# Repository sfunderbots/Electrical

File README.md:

# Electrical

This is a repository containing all of the electrical board designs of The Bots, including firmware for the chicker board, which is contained in that sub-folder. 

The robot contains five custom PCBs (not including the Raspberry Pi).

All five boards contained on our robot (six including the Raspberry Pi), for context, are listed as follows:
1. Raspberry Pi 4 - Main Robot Computer and link between the active running computer running our team's software
2. [Faceplate](https://github.com/sfunderbots/Electrical/tree/main/FacePlate) - Connector between Raspberry Pi and Midplate for CANBUS communication, peripherals, and LCD screen eyes
3. [Midplate](https://github.com/sfunderbots/Electrical/tree/main/MidPlate) - Battery input and power distribution (doubles as a mechanical chassis)
4. [Chicker](https://github.com/sfunderbots/Electrical/tree/main/Chicker) - High Voltage Flyback Capacitor Charger and Solenoid Driver
5. [Simovr](https://github.com/sfunderbots/Electrical/tree/main/PAC5527Driver) - A BLDC Motor Driver designed based on the Tinymovr platform in a smaller footprint
6. [Baseplate](https://github.com/sfunderbots/Electrical/tree/main/BasePlate) - Power distribution and CANBUS distribution for the Simovr's, and breakbeam circuits to detect the ball

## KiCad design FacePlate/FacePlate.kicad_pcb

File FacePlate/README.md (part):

# Faceplate Board V2 Documentation

## Overview
---

The Faceplate[^1], one of five of our robot's on board custom PCBs (not including the Raspberry Pi), is a connector and peripheral board between the Raspberry Pi and the rest of the robot system. As this documentation pertains to the Robocup Small Size League Autonomous Soccer, this documentation will be very specific in its use case. The new version of the faceplate incorporates connectors for mouse sensors (localization improvement) and an offboard IMU (placed closer to the center of the robot with less vibration). All five boards contained on our robot (six including the Raspberry Pi), for context, are listed as follows:
1. Raspberry Pi 4 - Main Robot Computer and link between the active running computer running our team's software
2. Faceplate[^1] - Connector between Raspberry Pi and Midplate for CANBUS communication, peripherals, and LCD screen eyes
3. Midplate - Battery input and power distribution (doubles as a mechanical chassis)
4. Chicker[^2] - High Voltage Flyback Capacitor Charger and Solenoid Driver
5. Simovr[^3] - A BLDC Motor Driver designed based on the Tinymovr platform in a smaller footprint
6. Baseplate - Power distribution and CANBUS distribution for the Simovr's, and breakbeam circuits to detect the ball

[^1]: Aptly named due to our robot's circular LCD displays
[^2]: Named after a combination of the flexibility of both kicking or chipping circuits
[^3]: Aptly named after its creator, Simon, and its reference design, the Tinymovr

The Faceplate can be seen on the front of our robot, with the eyes visible and the board covered by a 3D printed piece below:

This guide will serve as a way of a tutorial to design this or a similar board in your own projects, for which we recommend to use JLCPCB as a PCB manufacturer - wew users can register through the link below and receive up to $123 in coupons: [New User](https://jlcpcb.com/?from=Newv).1

## Schematics
---
  
For any of the following schematics, it is useful to group components into a schematic library file inside the EDA tool you are using - in this case, KiCad. Saving custom schematics ensures that when you update a board design you carry over any modifications like manufacturer part numbers, JLC part numbers (LCSC), price, etc. The following serves as an example for what information is useful to keep in the schematic part.

> [!TIP]
> If you select "edit symbol library", you will see that it opens up the library tab in KiCad, which has all of our parts listed. The same information for the LDO as above is here as well.
> <p align="center">
> 
> </p>

> [!IMPORTANT]
> You will need to add your library path to the .KICAD_SYM schematic library file, which stores all of your components. While separating the components into groups hasnt been done yet on our end due to time constraints, we recommend grouping these components by type in separate .KICAD_SYM files to increase productivity.
> <p align="center">
> 
> </p>

Additionally, for each symbol in your library, an associated footprint needs to be added to each symbol used in the schematics, which will be covered in the layout section.

### Power
From the midplate, the Faceplate receives a regulated 5V supply for the Raspberry Pi at 3A, including the CANBUS which is wired all throughout our robot for between-board communication. Specifically, this uses a JST XH connector, which is easily sourced among hobbyists. Then, the board also steps this down to 3.3V for the onboard logic circuits needed such as peripherals and LCD screens. Bypass and decoupling capacitors are needed on the Low Voltage Regulator (LDO) to help maintain power stability, and is chosen over a DC/DC converter due to low current requirements.

<div style="display: flex; gap: 10px;">

</div>

> [!NOTE]
> The part chosen as shown (SOT-223 package) can handle up to 1A of current, which was significantly over specification for our needs.

> [!TIP]
> Always remember to double check the current requirements and heat generation of your system, especially for power conversion!

### Connection to Raspberry Pi
Since the Raspberry Pi 4 has a 40x2 standard dupont style 2.54mm pitch connector, it is easiest to attach a board to board connector of the same type for this PCB. To line it up with the Raspberry Pi, it was easily accomplished by measuring the placement of the 40 pin header in a CAD program (in our case, Onshape) and comparing it to the PCB.

> [!IMPORTANT]
> Special consideration must be taken for ensuring no physical interferences between parts on the bottom layer and the Raspberry Pi, and the top layer to the LCD screens.

### LCD Displays (eyes)
Our LCD displays are a circular GC9A LCD display for which the board is then covered by custom-made 3D printed material for protection surrounding the eyes. Each display (and corresponding breakout board) attaches to a standard 7x1 Dupont style 2.54mm pitch connector, and includes decoupling power capacitors for the 3.3V logic rail to maintain chip operation during normal operating transients. The parts are organized into hierarchical sheets for better organization and viewing of schematics.

### CANBUS
In order to communicate on the CANBUS, one needs to convert the standard SPI interface on the Raspberry Pi to a CAN interface, using a CAN controller (MCP2515T), and a CAN transceiver (SN65HVD233). The CAN controller operates on an 8MHz clock and communicates with a CAN transceiver to send and receive commands over the CANBUS interface. As with the displays, the CAN interface is grouped into a hierarchical sheet to simplify organization.

### Mouse Sensors
Two 8-pin JST GH series connectors link the Raspberry Pi with two identical custom PCBs using a Pixart Imaging PMW3360DM-T2QU navigation sensor, which will be placed at the base of the robot on either side. This will provide significant improvement to our localization and control of the robot, incorporating precice movement of sensors near the surface of the playing field. 

The board files of the mouse sensor can be found on our github page under [PWM3360_PCB_JST](https://github.com/sfunderbots/Electrical/tree/main/pmw3360-pcb-main/pmw3360_pcb_jst), which was modified from the github user siderakb to add a JST connector.

### IMU
For this revision of the faceplate, we have removed the direct connection of the IMU on the faceplate in place of an external connector to be wired to an IMU, in our case chosen as a breakout board from Adafruit: [4438](https://www.adafruit.com/product/4438). This will provide accurate 6-DoF for the robot to improve robot control speed. This is connected using a 4 pin JST PH connector (Adafruit calls it the STEMMA QT QWIIC) which provides both power and data lines.

## Layout
---

The layout of this board and boards in general can be described by the following seven steps:
1. Footprint Libraries (for schematic)
2. Board Setup (Layers and Shape)
3. Part Placment
4. DRC Rules (including differential pairs)
5. Power routing (including zones / polygons)
6. Signal routing (best practices)
7. Custom Rule Areas (e.g. clearance / keepouts) 

The following image shows the overall layout of the board, where red refers to the top layer, blue refers to the bottom layer, green refers to the inner 1 / power layer, and orange refers to the inner 2 / ground layer. These planes on the board make up the 4 layers for the most common PCB to be fabricated, with power layers included for better power distribution, and signals routed generally on the top and bottom layers, if possible.

Below reference most of the important shortcuts on the top bar used in KiCad: On the far left shows the board setup, then on the right past the lock and unlock icons are the footprint library editor, footprint library browser, 3D viewer, import changes from schematic, and DRC rules. 

### Footprint Libraries
Setting up the footprints for each component can be accomplished manually or by downloading a footprint from an EDA library online. One should always consult the datasheet to confirm the validity of the suggested layout. As an example, the 3.3V LDO mentioned in the symbol library section is shown below. One should always verify the validity of a footprint by downloading the 3D model of the part so that the pins will have sufficient solder area and are easy enough to rework with a soldering iron. 

> [!NOTE]
> One can access pre-built footprint files for your EDA tool of choice from libraries such as [snapeda.com](https://www.snapeda.com/home/) or [ultralibrarian.com](https://www.ultralibrarian.com/) for example. Many more exist, but these are the most frequently used. Always remember to verify these footprints as they may not match the datasheet.

> [!IMPORTANT]
> It is especially important to pay attention to drill sizes on through hole parts, as even half a millimeter of difference from the part size may be enough to cause interference during fabrication. For this reason we always recommend to check the "confirm production files" and "confirm part placement", so that the JLCPCB engineers can review your board and catch any issues before they are manufactured.

Lastly, with the same process as the symbol libraries, you need to ensure the path to the footprint library exists in the global or project path directories, so that KiCad knows where to look for this board when you place parts.

### Board Setup
Clicking the gear icon in the top left of the screen on the PCB editor in KiCad, you can access the Board Setup menu. In this menu you can select the number of layers on your board you intend to use, using the "Physical Stackup" submenu, and can define the type of layer used to help KiCad understand how you intend to use this board by using the "Board Editor Layers" submenu. 

> [!NOTE]
> This menu can be confusing, but most of this information can be ignored as when you upload your design to JLCPCB the selection menu for PCB type and layer stackup types is all done on their website. Here, the most important thing to remember is simply to select the number of layers used - usually 2, 4 or 6 depending on complexity of the signal routing.
> <p align="center">
> 
></p>

The shape of the PCB can be defined by creating a bounding box (or whatever closed shape you prefer) with the Edge Cuts Layer. First clicking on the edge cuts layer on the side bar shown below you can define a PCB shape using lines or arcs to create the shape of the board. As long as it is a closed shape, this will work and you can check the 3D view to verify it cut properly. The following shows an example when your board shape is malformed versus closed. When the board shape is closed, the shape will be filled in with a subtle grey tone, and the 3D model will be formed.

<div style="display: flex; gap: 10px;">

</div>

> [!TIP]
> As one can see, it is not always obvious when a board shape is malformed as seen by the above example, where two lines were clearly removed but the overall shape looks the same. As a general rule, the board shape will always fit to the largest area KiCad sees as possible on the Edge Cuts layer, hence how below the shape does not follow any of the drawn lines below.
> 

### Part Placement
When placing parts on the PCB one should think ahead where the power routing will go. In this case, the I would anticipate that the 5V net for the Raspberry Pi would go near the edge of the board and wrap around to the rightmost pins on the 40 pin header, with the 3.3V being the main power plane on the board. Secondly, one should leave enough space around parts to make it easier to solder if rework must be completed, or if you are soldering the boards yourselves. For the faceplate below, you can see that it was ideal to put our power and CAN connector (JST XH 4 pin) on the same side as our power switch and power connector on the midplate. The rest of the components will be arranged in similar fashion leaving enough space for connecting vias for power connection.

To help your process in laying out the PCB parts, you can see the "ratnest" of white lines across the board, which show you where the pads will be connected according to the schematic. 

> [!IMPORTANT]
> It is also super important at this time to pay attention to any missing ratnest wires or pads that do not have any connection, which may be a mistake on the schematic. For this reason I always label my net names on the schematic so that when laying out the PCB it will be obvious if something is missing.

> [!TIP]
> It is always useful to include mounting holes on the PCB so that you can attach the board to an enclosure, which may not be necessary for prototyping but it will be necessary in the end - therefore getting it out of the way early will avoid headaches in the future!
>
> Lastly, one should avoid placing components too close to the edge of the board, especially if the board is panelized, as any stresses to the PCB may cause early failure in certain components, such as PCB mount capacitors (not radial caps). A guide about part placement for proper power and signal delivery can be seen on the JLCPCB website here: [JLCPCB design guidelines for placement and routing](https://jlcpcb.com/blog/pcb-design-guidelines-placement-and-routing).

### DRC Rules

On any board project, DRC rules should be set up so that you are generally following manufacturer specifications. You can view the capabilities of JLCPCB on their website [here](https://jlcpcb.com/capabilities/pcb-capabilities), and if I can find it there should be a downloadable file for DRC rules. In the case that this doesn't exist any more, these settings can be set up as follows:

The default constraints should be filled out first, which shows important rules which will dictate how the PCB is fabricated later. Important values to consider here are the minimum widths for trace widths and clearance/spacing (for which I tend to at least double the minimum specified by JLCPCB, as this only specifies an absolute minimum, but not a practical number to avoid noise and EMI), copper to hole, and copper to edge clearances.

Additionally, you can include DRC rules by setting up Net Classes in the schematic with colors, and in the PCB you can select these net classes to choose specific clearance and widths based on the expected current on those traces. The following shows the example of the "Power" Net Class which I have colored orange for example.

For these specific nets, I have selected a slightly larger default via size (0.7/0.35mm) with larger overall trace width minimum. Generally speaking with larger trace widths the larger the clearance should be as well. 

> [!TIP]
> It is advisable to consult a PCB calculator for non-logic level trace and via sizing, such as [Saturn PCB Toolkit](https://saturnpcb.com/saturn-pcb-toolkit/).
>
> Secondly, always check your DRC rules BEFORE you start routing component tracks. This way, you will ensure there are no part placement conflicts or issues with footprints you will have to solve later and re-route components. To ensure components are not conflicting in 3D space, the pink courtyards must not overlap.

> [!WARNING]
> It is important not to look over any DRC warnings and especially errors, I would only recommend setting a DRC rule to "ignore" if it is absolutely necessary (set in "Violation Severity" under board setup design rules), as this can cause issues to be forgotten about especially when a lot of errors that seem meaningless show up can mask a significant board error if those are ignored.
 
### Power Routing

Moving on to power routing, we can set up zones (or polygons depending on what EDA tool you use) of copper that will fill in our board layers and make up our copper planes. For a 4 layer board such as this one, I generally recommend filling in ground on 3 of the four layers and power on one of the two internal power planes. This enables easy routing for power delivery to most components, assuming one (or more depending on current draw) correctly sized vias are used. 

On this image above, you can see the zone created, where on the power layer we have a thick trace going from the 5V connector to the Raspberry Pi 40 pin header. 

> [!IMPORTANT]
> It should be noted that at 3A and below the return current here does not matter as much, but on a design that pulls more than 10A I would recommend matching the return ground plane such that the return current goes directly underneath the power trace.

Additionally, each component includes power vias to connect to the 3.3V and GND planes of the board, which are sized slightly bigger for extra margin.

### Signal Routing

With the power traces routed on the board, signals are the next thing I would consider. 

> [!TIP]
> Remember to keep the inner layers as power distribution as much as possible avoiding signals on those layers, as it could increase noise on the signals.

For recommended trace widths, I tend to use anywhere from 8-10mil traces for signals, depending on space. It is advisable to not decrease the size too much, as it may become hard for your PCB manufacturer (such as JLCPCB in our case) to manufacture. On the other end, having a trace width too large may impact impedance of the line, if you are designing a higher speed communication board. 

> [!TIP]
> For most signal traces, the trace width isn't super important at this range, as long as its big enough for the load expected. JLCPCB has a handy guide in determining the trace width of a PCB trace.

With most signal traces, it is recommended to try and maintain a standardized pattern of top and bottom layers for either horizontal or vertical traces, to permit densely populated routing without causing too much hassle. This can be seen with the PCB design in the full layout shown earlier.

### Custom Rule Areas

In some cases, you may have ICs on your board that have very fine pitch (such as the TSSOP-20 Can Controller), and your standard DRC rule clearances may not work here if your overall clearance is larger. In this case, you can temporarily shrink the clearance required around this chip by adding a custom rule area with all the toggles turned off (so that it does not exclude copper, pads, footprints, etc) for which we will add a custom rule later. The fine pitch chip is shown below, with a zone created around it and all options deselected.

With this we can now go into the DRC rule editor (much easier than custom rules in the board setup tab in older KiCad versions) and add a custom fine pitch spacing rule. This can be found from Tools -> DRC rule editor.

Here, object A refers to the currently-being-routed track, via, or other item, where the new clearance rule now only gets applied inside this area. There are multiple ways to accomplish the same feature with custom rulests, and there are a lot of other use cases that you can explore - this is only an example. 

> [!TIP]
> KiCad has a previous version guide (pre-V10) about custom rules and their use cases, so please feel free to use [this guide](https://forum.kicad.info/t/custom-design-rules-examples/43987/2) to your liking. There are also a lot of github links that people have made including JLCPCB specific rulesets you can use if you search these up.

## Implementation
---

To fabricate the boards, we used JLCPCB, which has been extremely reliable for countless hobby projects over the last five years. Here’s JLC's new user [6-layer PCB coupon](https://jlcpcb.com/6-layer-pcb?from=social) which saves you 30$ on your project so you can start a project with relatively low cost. 

Apart from being a reliable PCB manufacturer, JLCPCB has also been very cost effective - on their part library website, you can find alternate components from their partner LCSC to make board projects feasible at lower cost with similar or the same specifications. 

However, before you fabricate the boards, you need to run a DRC check, under Inspect -> Design Rules Checker. This ensures that any clearance violations (short-circuits), unconnected nets (any traces you forgot to route), or trace widths that are out of the Net Class spec.

> [!IMPORTANT]
> For this very reason, it is highly advisable, while not strictly necessary, to set up different Net Classes and assign them in the schematic by right clicking the wire. With a larger trace width for a high current trace set, this will ensure that when you go to manufacture your boards that trace will not burn up from too little copper area to conduct the required current, with the DRC check ensuring you fix the mistake before this stage.

For this board specifically, Net Class rules didn't need to be set up as it is a relatively simple board and my knowledge is sufficient to accomplish it without any major hiccups, knowing the rough sizing for traces we need. At a very minimum, it is recommended to use the toolkit recommended earlier ([Saturn PCB Toolkit](https://saturnpcb.com/saturn-pcb-toolkit/)) to verify that your trace width will sufficiently carry the current without heating up too much.

Clicking the 3D model view in KiCad (the icon that looks like a capacitor) you can view the 3D model of the board - the Faceplate looks as follows:

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
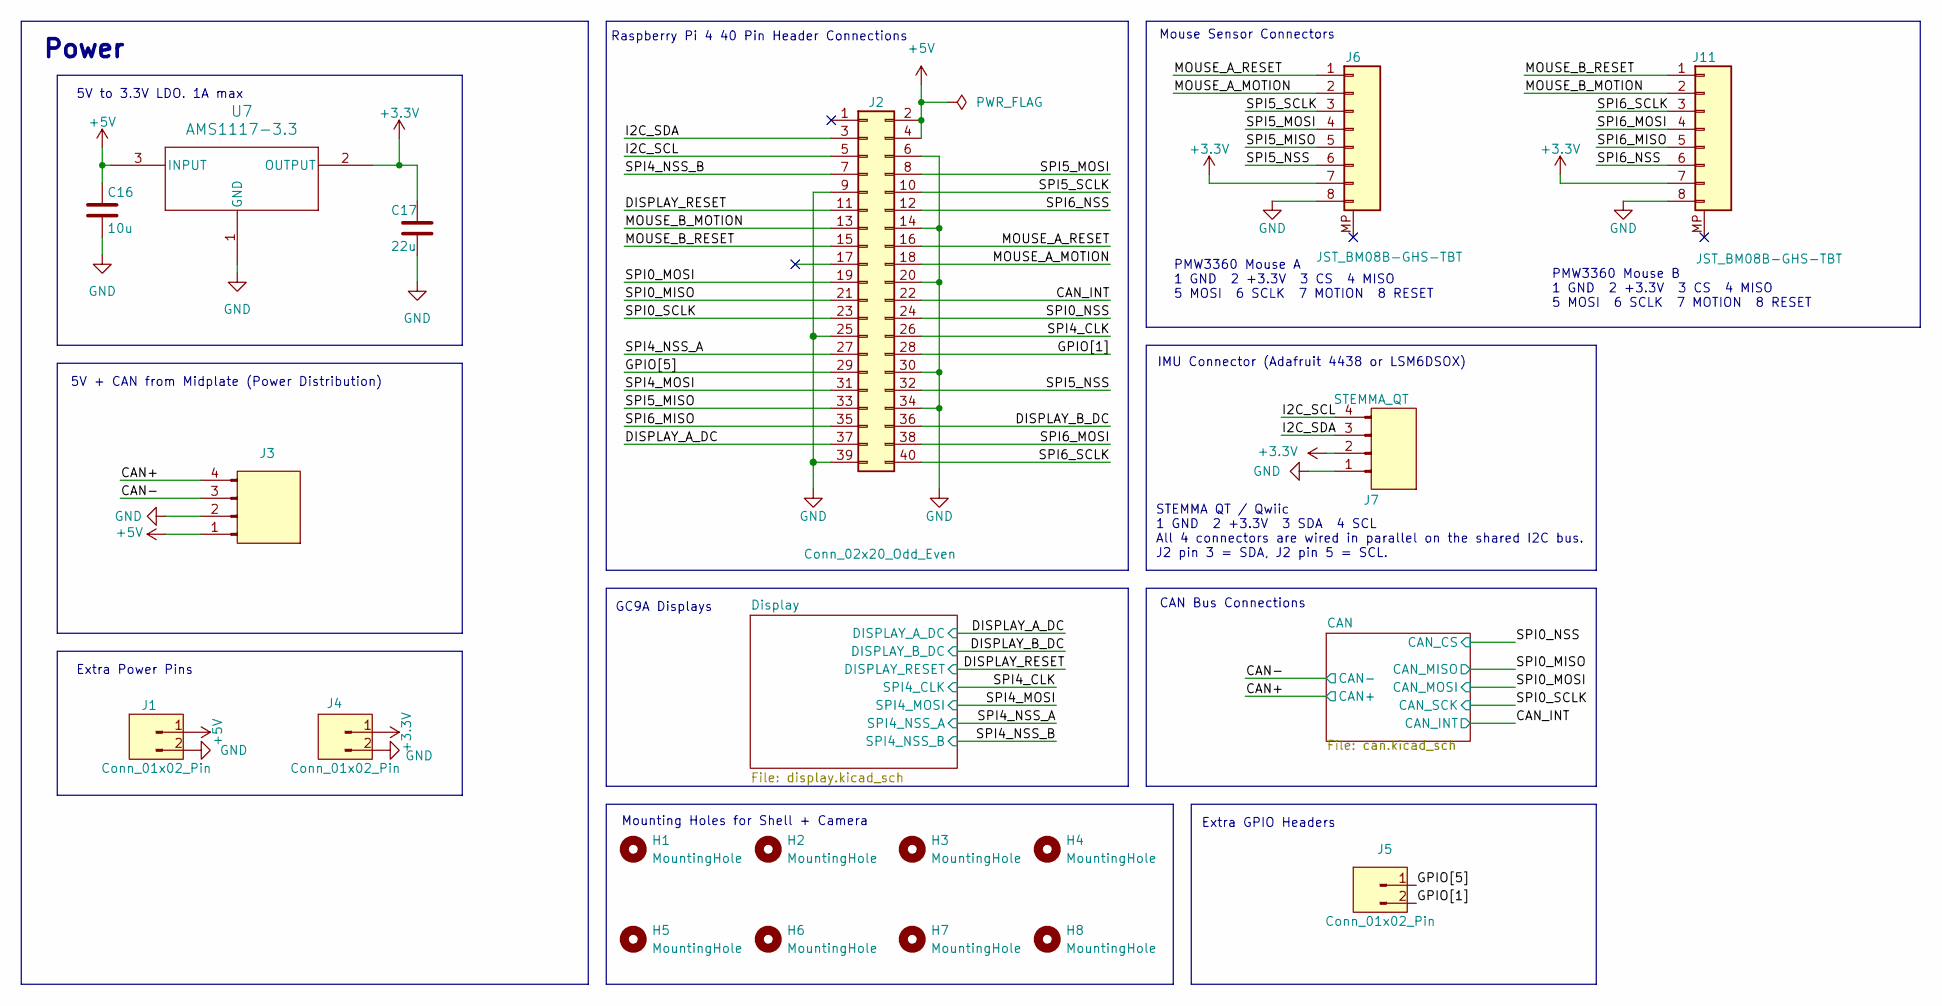
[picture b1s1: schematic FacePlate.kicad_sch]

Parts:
C16: 10u; C_0805_2012Metric; MPN GRM21BR61H106KE43L; LCSC C440198
C17: 22u; C_0603_1608Metric; LCSC C59461
H1, H2, H3, H4, H5, H6, H7, H8: MountingHole
J1, J4, J5: Conn_01x02_Pin; PinHeader_1x02_P2.54mm_Vertical
J2: Conn_02x20_Odd_Even; PinSocket_2x20_P2.54mm_Horizontal
J3: Conn_01x04_Pin; JST_XH_B4B-XH-AM_1x04_P2.50mm_Vertical
J6, J11: JST_BM08B-GHS-TBT; JST_BM08B-GHS-TBT_LF__SN__N_; MPN BM08B-GHS-TBT(LF)(SN); LCSC C133062
J7: STEMMA_QT; JST_SH_BM04B-SRSS-TB_1x04-1MP_P1.00mm_Vertical
U7: AMS1117-3.3; SOT-223-3_TabPin2; MPN AMS1117-3.3; LCSC C6186

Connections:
+3.3V: C17.1, J4.1, J6.7, J7.2, J11.7, U7.2 (OUTPUT); also elsewhere on the board
+5V: C16.1, J1.1, J2.2, J2.4, J3.1, U7.3 (INPUT)
/CAN+: J3.4; also elsewhere on the board
/CAN-: J3.3; also elsewhere on the board
/CAN_INT: J2.22; also elsewhere on the board
/DISPLAY_A_DC: J2.37; also elsewhere on the board
/DISPLAY_B_DC: J2.36; also elsewhere on the board
/DISPLAY_RESET: J2.11; also elsewhere on the board
/GPIO[1]: J2.28, J5.2
/GPIO[5]: J2.29, J5.1
/I2C_SCL: J2.5, J7.4
/I2C_SDA: J2.3, J7.3
/MOUSE_A_MOTION: J2.18, J6.2
/MOUSE_A_RESET: J2.16, J6.1
/MOUSE_B_MOTION: J2.13, J11.2
/MOUSE_B_RESET: J2.15, J11.1
/SPI0_MISO: J2.21; also elsewhere on the board
/SPI0_MOSI: J2.19; also elsewhere on the board
/SPI0_NSS: J2.24; also elsewhere on the board
/SPI0_SCLK: J2.23; also elsewhere on the board
/SPI4_CLK: J2.26; also elsewhere on the board
/SPI4_MOSI: J2.31; also elsewhere on the board
/SPI4_NSS_A: J2.27; also elsewhere on the board
/SPI4_NSS_B: J2.7; also elsewhere on the board
/SPI5_MISO: J2.33, J6.5
/SPI5_MOSI: J2.8, J6.4
/SPI5_NSS: J2.32, J6.6
/SPI5_SCLK: J2.10, J6.3
/SPI6_MISO: J2.35, J11.5
/SPI6_MOSI: J2.38, J11.4
/SPI6_NSS: J2.12, J11.6
/SPI6_SCLK: J2.40, J11.3
GND: C16.2, C17.2, J1.2, J2.6, J2.9, J2.14, J2.20, J2.25, J2.30, J2.34, J2.39, J3.2, J4.2, J6.8, J7.1, J11.8, U7.1 (GND); also elsewhere on the board

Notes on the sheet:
Mounting Holes for Shell + Camera
STEMMA QT / Qwiic 1 GND 2 +3.3V 3 SDA 4 SCL All 4 connectors are wired in parallel on the shared I2C bus. J2 pin 3 = SDA, J2 pin 5 = SCL.
Extra GPIO Headers
PMW3360 Mouse A 1 GND 2 +3.3V 3 CS 4 MISO 5 MOSI 6 SCLK 7 MOTION 8 RESET
Raspberry Pi 4 40 Pin Header Connections
GC9A Displays
IMU Connector (Adafruit 4438 or LSM6DSOX)
CAN Bus Connections
5V + CAN from Midplate (Power Distribution)
Mouse Sensor Connectors
Power
5V to 3.3V LDO. 1A max
PMW3360 Mouse B 1 GND 2 +3.3V 3 CS 4 MISO 5 MOSI 6 SCLK 7 MOTION 8 RESET
Extra Power Pins

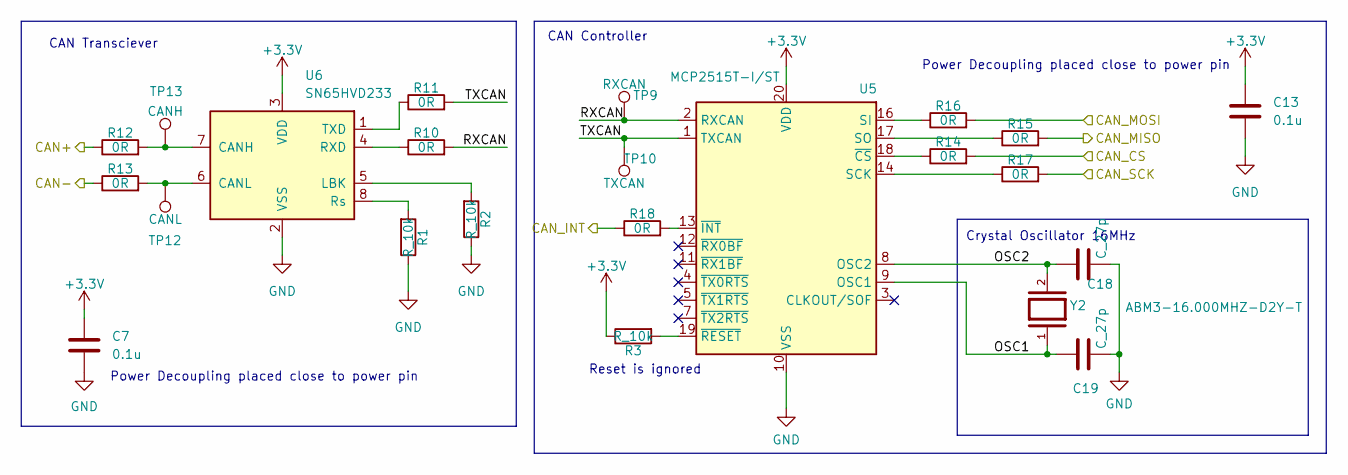
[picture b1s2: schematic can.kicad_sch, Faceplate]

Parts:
C7, C13: 0.1u; C_0603_1608Metric; MPN CC0603KRX7R9BB104; LCSC C14663
C18, C19: C_27p; C_0603_1608Metric; MPN CC0603JRNPO9BN270; JLC 0603
R1, R2, R3: R_10k; R_0603_1608Metric; MPN 0603WAF1002T5E; LCSC C25804
R10, R11, R12, R13, R14, R15, R16, R17, R18: 0R; R_0603_1608Metric; MPN 0603WAF0000T5E; LCSC C21189
TP9: RXCAN; TestPoint_Pad_D1.0mm
TP10: TXCAN; TestPoint_Pad_D1.0mm
TP12: CANL; TestPoint_Pad_D1.0mm
TP13: CANH; TestPoint_Pad_D1.0mm
U5: MCP2515T-I/ST; TSSOP-20_4.4x6.5mm_P0.65mm; MPN MCP2515T-I/ST; LCSC C185941
U6: SN65HVD233; SOIC-8_3.9x4.9mm_P1.27mm; MPN SN65HVD233; JLC 8-SOIC
Y2: ABM3-16.000MHZ-D2Y-T; ABM3; MPN ABM3-16.000MHZ-D2Y-T; JLC SMD5032-2P

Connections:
+3.3V: C7.1, C13.1, R3.1, U5.20 (VDD), U6.3 (VDD); also elsewhere on the board
/CAN+: R12.1; also elsewhere on the board
/CAN-: R13.1; also elsewhere on the board
/CAN/OSC1: C19.1, U5.9 (OSC1), Y2.1
/CAN/OSC2: C18.1, U5.8 (OSC2), Y2.2
/CAN/RXCAN: R10.2, TP9.1 (1_1), U5.2 (RXCAN)
/CAN/TXCAN: R11.2, TP10.1 (1_1), U5.1 (TXCAN)
/CAN_INT: R18.1; also elsewhere on the board
/SPI0_MISO: R15.2; also elsewhere on the board
/SPI0_MOSI: R16.2; also elsewhere on the board
/SPI0_NSS: R14.2; also elsewhere on the board
/SPI0_SCLK: R17.2; also elsewhere on the board
GND: C7.2, C13.2, C18.2, C19.2, R1.1, R2.1, U5.10 (VSS), U6.2 (VSS); also elsewhere on the board
unnamed: R17.1, U5.14 (SCK)
unnamed: R16.1, U5.16 (SI)
unnamed: R15.1, U5.17 (SO)
unnamed: R14.1, U5.18 (~CS)
unnamed: R18.2, U5.13 (~INT)
unnamed: R3.2, U5.19 (~RESET)
unnamed: R12.2, TP13.1 (1_1), U6.7 (CANH)
unnamed: R13.2, TP12.1 (1_1), U6.6 (CANL)
unnamed: R2.2, U6.5 (LBK)
unnamed: R10.1, U6.4 (RXD)
unnamed: R1.2, U6.8 (Rs)
unnamed: R11.1, U6.1 (TXD)

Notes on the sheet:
Power Decoupling placed close to power pin
CAN Controller
CAN Transciever
Reset is ignored
Crystal Oscillator 16MHz

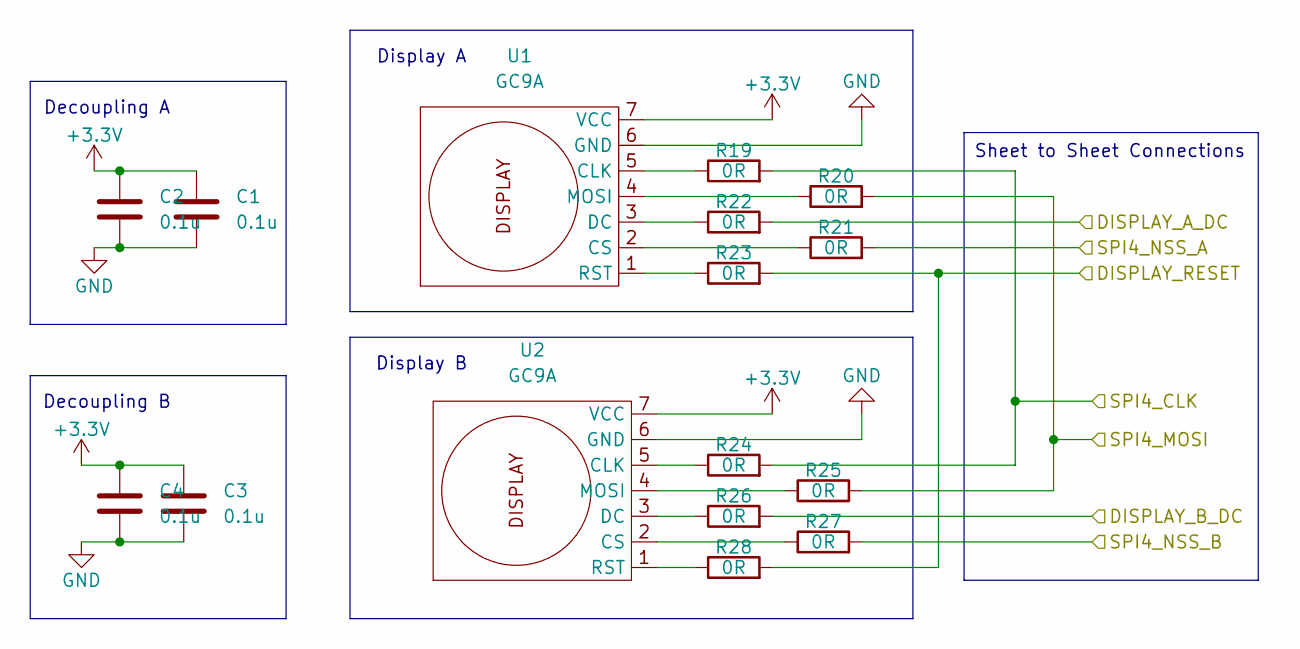
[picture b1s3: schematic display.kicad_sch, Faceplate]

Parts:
C1, C2, C3, C4: 0.1u; C_0603_1608Metric; MPN CC0603KRX7R9BB104; LCSC C14663
R19, R20, R21, R22, R23, R24, R25, R26, R27, R28: 0R; R_0603_1608Metric; MPN 0603WAF0000T5E; LCSC C21189
U1, U2: GC9A; GC9A_Display

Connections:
+3.3V: C1.1, C2.1, C3.1, C4.1, U1.7 (VCC), U2.7 (VCC); also elsewhere on the board
/DISPLAY_A_DC: R22.2; also elsewhere on the board
/DISPLAY_B_DC: R26.2; also elsewhere on the board
/DISPLAY_RESET: R23.2, R28.2; also elsewhere on the board
/SPI4_CLK: R19.2, R24.2; also elsewhere on the board
/SPI4_MOSI: R20.2, R25.2; also elsewhere on the board
/SPI4_NSS_A: R21.2; also elsewhere on the board
/SPI4_NSS_B: R27.2; also elsewhere on the board
GND: C1.2, C2.2, C3.2, C4.2, U1.6 (GND), U2.6 (GND); also elsewhere on the board
unnamed: R19.1, U1.5 (CLK)
unnamed: R21.1, U1.2 (CS)
unnamed: R22.1, U1.3 (DC)
unnamed: R20.1, U1.4 (MOSI)
unnamed: R23.1, U1.1 (RST)
unnamed: R24.1, U2.5 (CLK)
unnamed: R27.1, U2.2 (CS)
unnamed: R26.1, U2.3 (DC)
unnamed: R25.1, U2.4 (MOSI)
unnamed: R28.1, U2.1 (RST)

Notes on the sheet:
Display B
Display A
Decoupling B
Decoupling A
Sheet to Sheet Connections

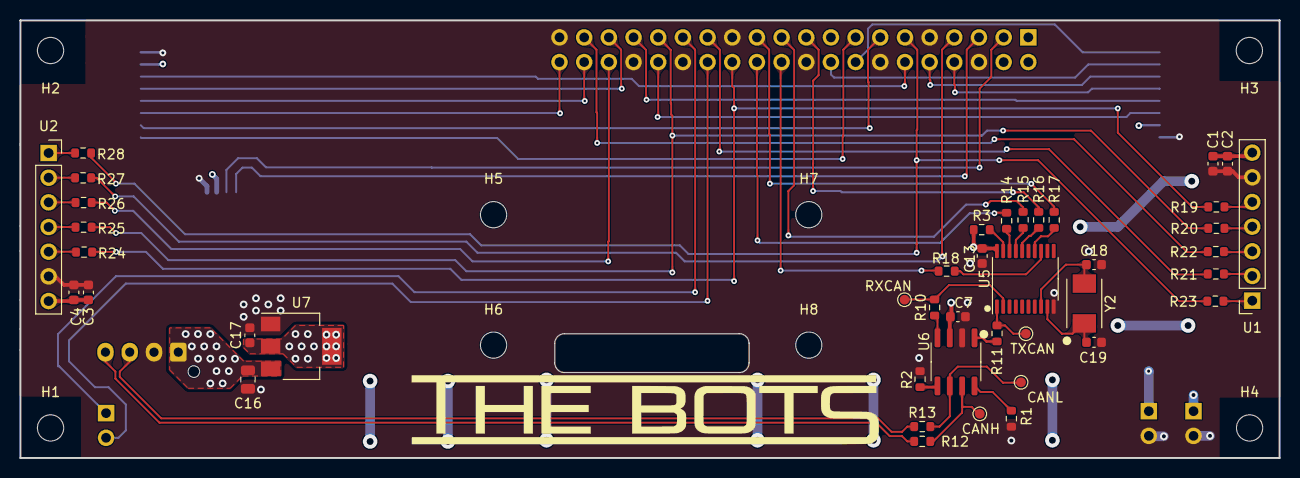
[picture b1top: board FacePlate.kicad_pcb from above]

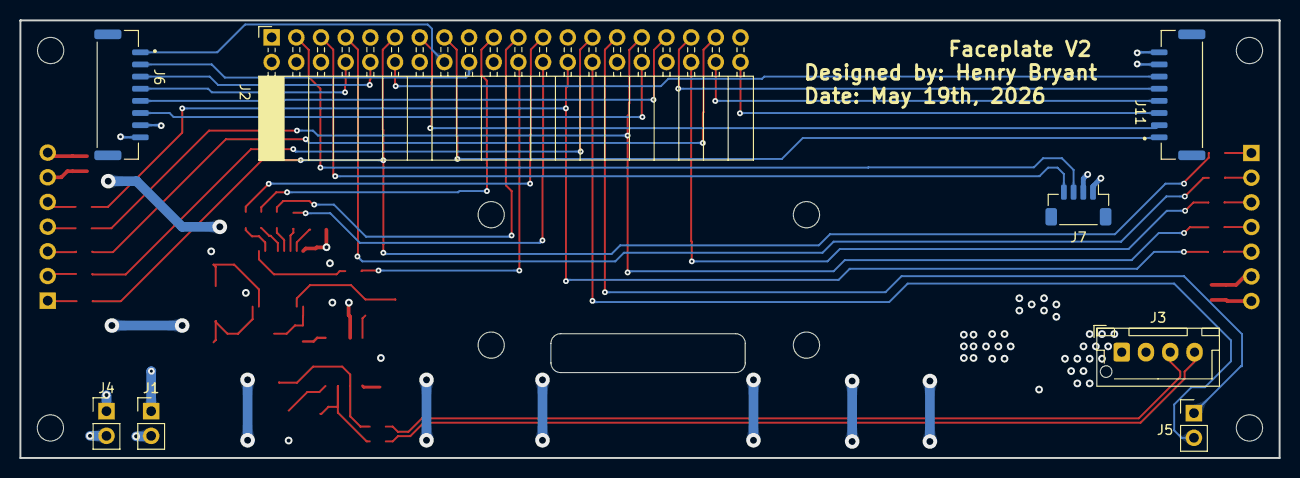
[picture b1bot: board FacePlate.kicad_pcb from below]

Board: 4 copper layers, 129.6 x 45.0 mm, 58 parts (8 on the bottom side), 59 nets.

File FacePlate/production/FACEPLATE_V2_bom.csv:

Designator,Footprint,Quantity,Value,LCSC Part #
"C1, C13, C2, C3, C4, C7",0603,6,0.1u,C14663
C16,0805,1,10u,C440198
C17,0603,1,22u,C59461
"C18, C19",0603,2,C_27p,C107045
"J1, J4, J5",PinHeader_1x02_P2.54mm_Vertical,3,Conn_01x02_Pin,
"J11, J6",JST_BM08B-GHS-TBT_LF__SN__N_,2,JST_BM08B-GHS-TBT,C133062
J2,PinSocket_2x20_P2.54mm_Horizontal,1,Conn_02x20_Odd_Even,
J3,JST_XH_B4B-XH-AM_1x04_P2.50mm_Vertical,1,Conn_01x04_Pin,
J7,JST_SH_BM04B-SRSS-TB_1x04-1MP_P1.00mm_Vertical,1,STEMMA_QT,
"R1, R2, R3",0603,3,R_10k,C25804
"R10, R11, R12, R13, R14, R15, R16, R17, R18, R19, R20, R21, R22, R23, R24, R25, R26, R27, R28",0603,19,0R,C21189
TP10,TestPoint_Pad_D1.0mm,1,TXCAN,
TP12,TestPoint_Pad_D1.0mm,1,CANL,
TP13,TestPoint_Pad_D1.0mm,1,CANH,
TP9,TestPoint_Pad_D1.0mm,1,RXCAN,
"U1, U2",GC9A_Display,2,GC9A,
U5,TSSOP-20_4.4x6.5mm_P0.65mm,1,MCP2515T-I/ST,C185941
U6,SOIC-8_3.9x4.9mm_P1.27mm,1,SN65HVD233,C61643
U7,SOT-223-3_TabPin2,1,AMS1117-3.3,C6186
Y2,ABM3,1,ABM3-16.000MHZ-D2Y-T,C596861

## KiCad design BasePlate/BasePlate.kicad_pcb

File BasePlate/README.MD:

# Baseplate Board Documentation

This board is a power distribution and CANBUS distribution board, including the breakbeam connection to easily connect all motor drivers while disconnecting the top half and bottom half of the robot with just a few connections. This includes Power, CAN, and breakbeam cables.

## License
This project is licensed under the MIT License - see the [LICENSE](LICENSE) file for details.

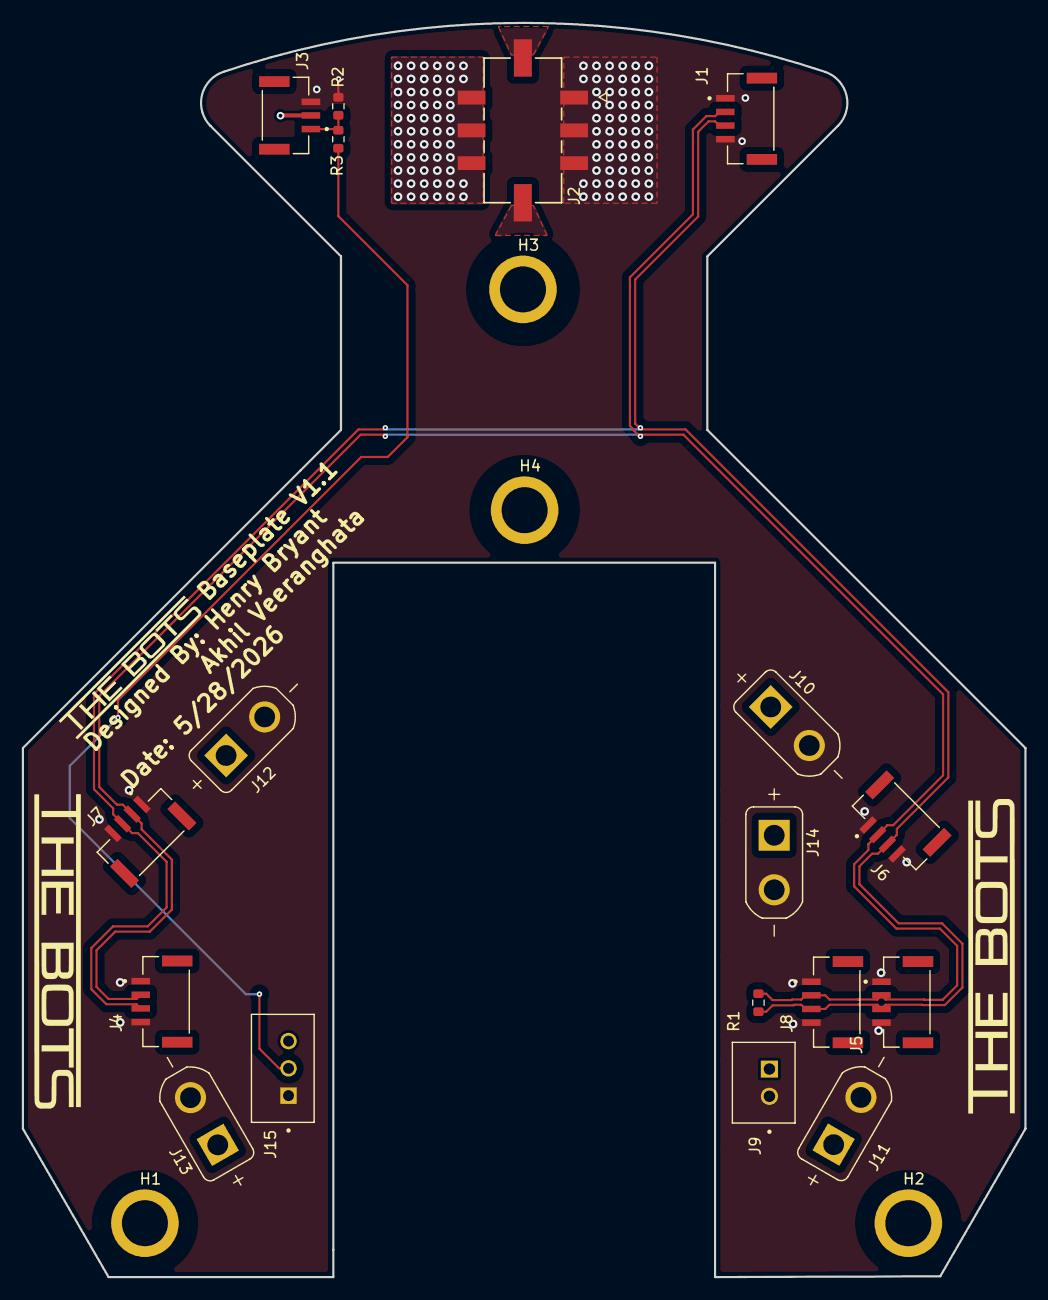
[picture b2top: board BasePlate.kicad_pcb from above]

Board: 4 copper layers, 91.9 x 115.0 mm, 22 parts (0 on the bottom side), 7 nets.

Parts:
H1, H2, H3, H4: SMTSO2515CTJ
J1, J4, J5, J6, J7, J8: JST_BM04B-GHS-TBT
J2: 1586842-6; TE_1586842-6_6PIN
J3: JST_BM03B-GHS-TBT
J9: XH 2 Pin; JST_B2B-XH-A_LF__SN_
J10, J11, J12, J13, J14: XT30UPB-M; AMASS_XT30UPB-M
J15: JST_B3B-XH-A
R1: 120R; R_0603_1608Metric
R2: 20k; R_0603_1608Metric
R3: 10k; R_0603_1608Metric

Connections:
+5V: J3.2, J9.2, J15.3
/CAN_N: J1.3, J4.3, J5.3, J6.3, J7.3, J8.3, R1.1
/CAN_P: J1.2, J4.2, J5.2, J6.2, J7.2, J8.2, R1.2
BKBM: J15.2, R3.1
GND: J1.1, J1.4, J2.1, J2.2, J2.3, J3.3, J4.1, J4.4, J5.1, J5.4, J6.1, J6.4, J7.1, J7.4, J8.1, J8.4, J9.1, J10.N, J11.N, J12.N, J13.N, J14.N, J15.1, R2.2
unnamed: J3.1, R2.1, R3.2
VCC: J2.4, J2.5, J2.6, J10.P, J11.P, J12.P, J13.P, J14.P

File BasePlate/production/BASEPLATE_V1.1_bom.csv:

Designator,Footprint,Quantity,Value,LCSC Part #
"H1, H2, H3, H4",SMTSO2515CTJ,4,SMTSO2515CTJ,C2915629
"J1, J4, J5, J6, J7, J8",JST_BM04B-GHS-TBT,6,JST_BM04B-GHS-TBT,C161692
"J10, J11, J12, J13, J14",AMASS_XT30UPB-M,5,XT30UPB-M,
J15,JST_B3B-XH-A,1,JST_B3B-XH-A,B3B-XH-A(LF)(SN)
J2,TE_1586842-6_6PIN,1,1586842-6,
J3,JST_BM03B-GHS-TBT,1,JST_BM03B-GHS-TBT,C161691
J9,JST_B2B-XH-A_LF__SN_,1,XH 2 Pin,
R1,0603,1,120R,C22787
R2,0603,1,20k,
R3,0603,1,10k,

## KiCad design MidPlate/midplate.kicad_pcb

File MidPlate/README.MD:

# Midplate Board Documentation

This board is a power distribution board, including  battery input, reverse polarity protection, power pillars for the chicker board, and a power switch to control power. The board is designed in KiCad, available on this project repository.

This version is from 2024, published in 2026. The midplate had one failure in the past where a threaded SMT insert had failed due to over-torque, but has only had one such occurrence. 

## License
This project is licensed under the MIT License - see the [LICENSE](LICENSE) file for details.

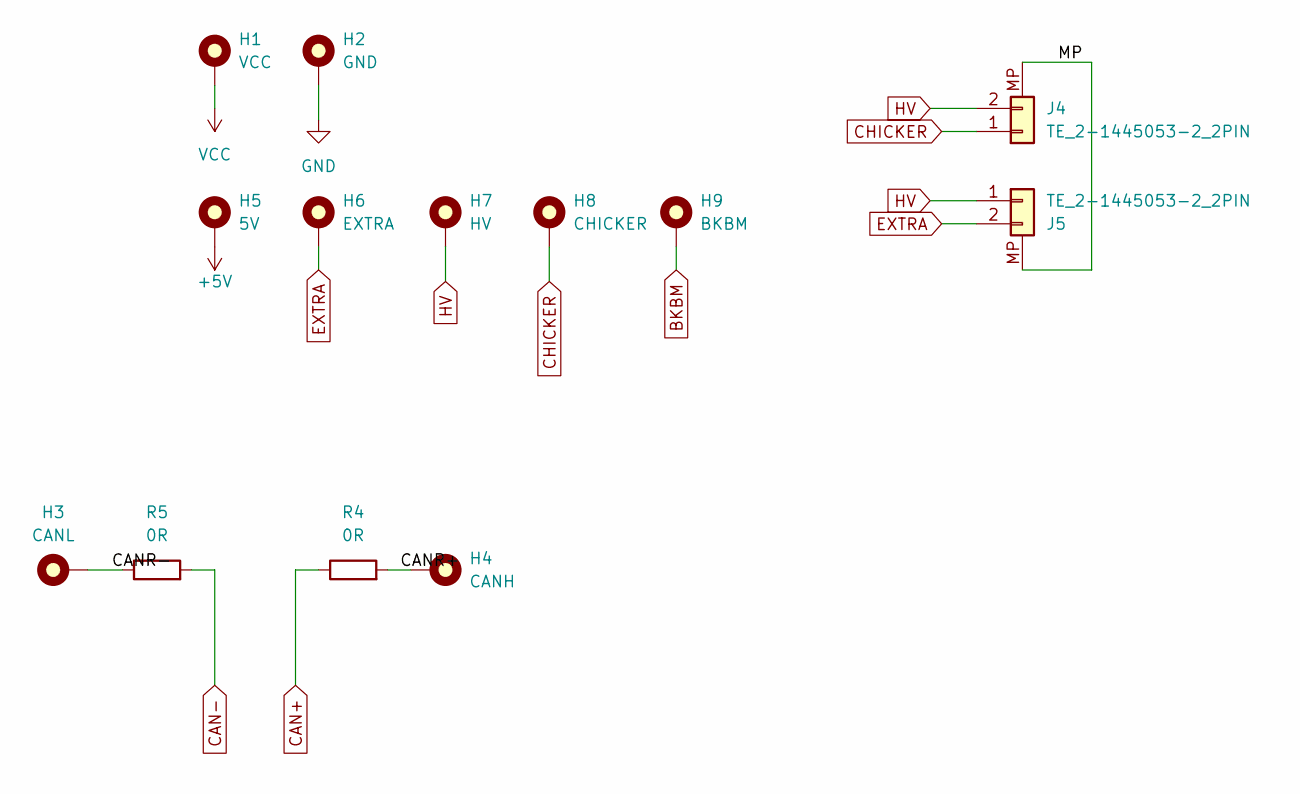
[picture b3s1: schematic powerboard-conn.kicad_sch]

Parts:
H1: VCC; SMTSO2515CTJ; LCSC C2915629
H2: GND; SMTSO2515CTJ; LCSC C2915629
H3: CANL; SMTSO2515CTJ; LCSC C2915629
H4: CANH; SMTSO2515CTJ; LCSC C2915629
H5: 5V; SMTSO2515CTJ; LCSC C2915629
H6: EXTRA; SMTSO2515CTJ; LCSC C2915629
H7: HV; SMTSO2515CTJ; LCSC C2915629
H8: CHICKER; SMTSO2515CTJ; LCSC C2915629
H9: BKBM; SMTSO2515CTJ; LCSC C2915629
J4, J5: TE_2-1445053-2_2PIN; MPN 2-1445053-2
R4, R5: 0R; R_0603_1608Metric; MPN 0603WAF0000T5E; JLC 0603

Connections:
+5V: H5.1 (1_1); also elsewhere on the board
/Power Board Connections/CANR+: H4.1 (1_1), R4.2
/Power Board Connections/CANR-: H3.1 (1_1), R5.1
/Power Board Connections/MP: J4.MP, J5.MP
BKBM: H9.1 (1_1); also elsewhere on the board
CAN+: R4.1; also elsewhere on the board
CAN-: R5.2; also elsewhere on the board
CHICKER: H8.1 (1_1), J4.1
EXTRA: H6.1 (1_1), J5.2
GND: H2.1 (1_1); also elsewhere on the board
HV: H7.1 (1_1), J4.2, J5.1
VCC: H1.1 (1_1); also elsewhere on the board

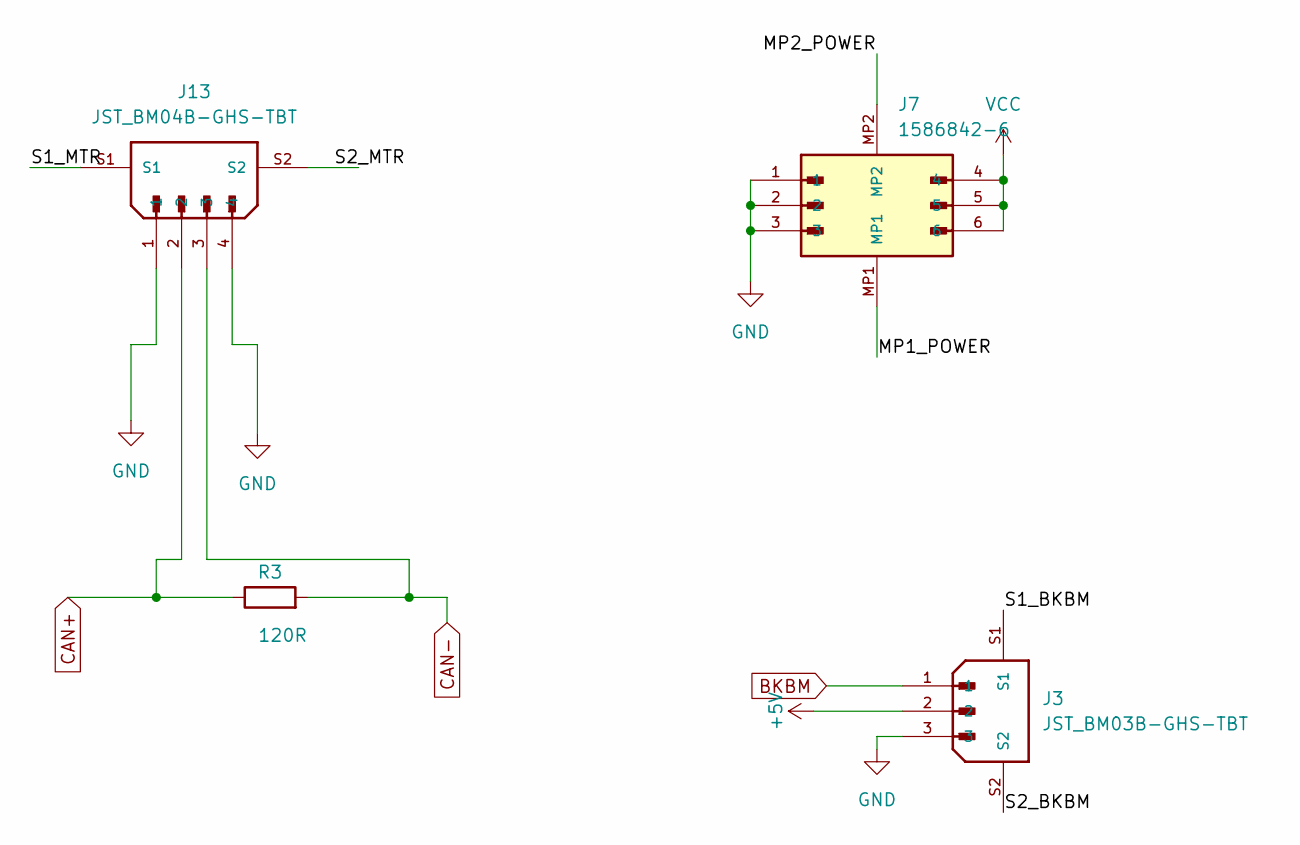
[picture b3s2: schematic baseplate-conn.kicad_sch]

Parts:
J3: JST_BM03B-GHS-TBT; MPN BM03B-GHS-TBT
J7: 1586842-6; TE_1586842-6_6PIN
J13: JST_BM04B-GHS-TBT; MPN BM04B-GHS-TBT
R3: 120R; R_0603_1608Metric; MPN 0603WAF1200T5E; JLC 0603

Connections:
+5V: J3.2; also elsewhere on the board
/Baseplate Connections/MP1_POWER: J7.MP1
/Baseplate Connections/MP2_POWER: J7.MP2
/Baseplate Connections/S1_BKBM: J3.S1
/Baseplate Connections/S1_MTR: J13.S1
/Baseplate Connections/S2_BKBM: J3.S2
/Baseplate Connections/S2_MTR: J13.S2
BKBM: J3.1; also elsewhere on the board
CAN+: J13.2, R3.1; also elsewhere on the board
CAN-: J13.3, R3.2; also elsewhere on the board
GND: J3.3, J7.1, J7.2, J7.3, J13.1, J13.4; also elsewhere on the board
VCC: J7.4, J7.5, J7.6; also elsewhere on the board

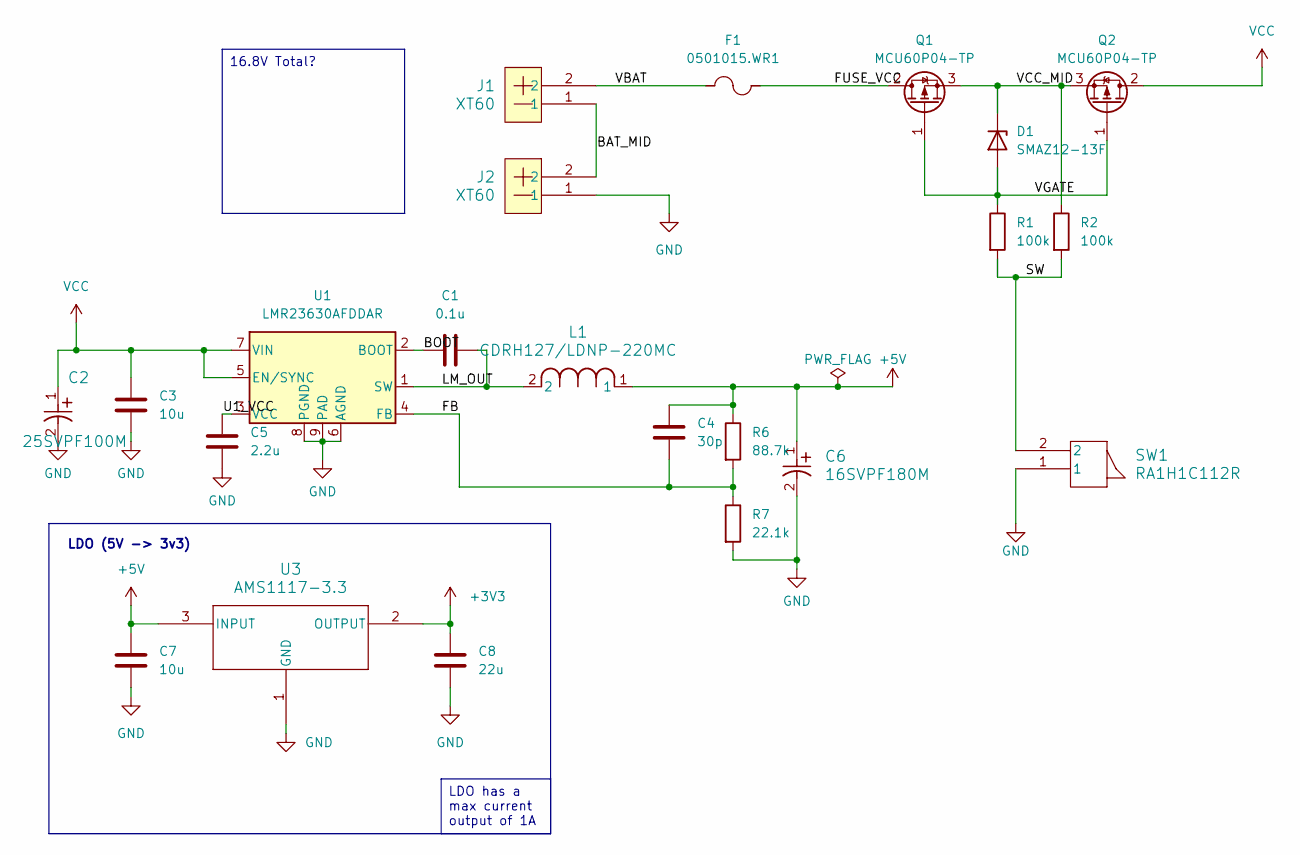
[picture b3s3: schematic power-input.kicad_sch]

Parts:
C1: 0.1u; C_0603_1608Metric; MPN CC0603KRX7R9BB104; JLC 0603
C2: 25SVPF100M; CAP_25SVPF100M; LCSC C136279
C3, C7: 10u; C_0805_2012Metric; MPN GRM21BR61H106KE43L; JLC 0805
C4: 30p; C_0603_1608Metric; MPN CC0603JRNPO9BN270; JLC 0603
C5: 2.2u; C_1206_3216Metric; JLC 1206
C6: 16SVPF180M; CAP_16SVPF180M; LCSC C136277
C8: 22u; C_0603_1608Metric; LCSC C59461
D1: SMAZ12-13F; D_SMB; MPN SMAZ12-13F; LCSC C260227
F1: 0501015.WR1; Fuse_1206_3216Metric; MPN 0501015.WR1; JLC 1206
J1, J2: XT60; XT60_12-14AWG_POWER
L1: CDRH127/LDNP-220MC; IND_CDRH127_LDNP-470MC_SUM; LCSC C879420
Q1, Q2: MCU60P04-TP; DPAK-3_ONS; LCSC C130101
R1, R2: 100k; R_0603_1608Metric; MPN 0603WAF1003T5E; JLC 0603
R6: 88.7k; R_0603_1608Metric; MPN 0603WAF4752T5E; JLC 0603
R7: 22.1k; R_0603_1608Metric; MPN 0603WAF4752T5E; JLC 0603
SW1: RA1H1C112R; SW_RA1H1C112R
U1: LMR23630AFDDAR; TI_SO-PowerPAD-8_ThermalVias; MPN LMR23630AFDDAR; JLC SO-8
U3: AMS1117-3.3; SOT-223-3_TabPin2; MPN AMS1117-3.3; JLC SOT-223

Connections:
+5V: C4.1, C6.1, C7.1, L1.1, R6.1, U3.3 (INPUT); also elsewhere on the board
/Power Input/BAT_MID: J1.1, J2.2
/Power Input/BOOT: C1.1, U1.2 (BOOT)
/Power Input/FB: C4.2, R6.2, R7.1, U1.4 (FB)
/Power Input/FUSE_VCC: F1.2, Q1.2 (D)
/Power Input/LM_OUT: C1.2, L1.2, U1.1 (SW)
/Power Input/SW: R1.2, R2.2, SW1.2
/Power Input/U1_VCC: C5.1, U1.3 (VCC)
/Power Input/VBAT: F1.1, J1.2
/Power Input/VCC_MID: D1.1 (K), Q1.3 (S), Q2.3 (S), R2.1
/Power Input/VGATE: D1.2 (A), Q1.1 (G), Q2.1 (G), R1.1
GND: C2.2, C3.2, C5.2, C6.2, C7.2, C8.2, J2.1, R7.2, SW1.1, U1.6 (AGND), U1.8 (PGND), U1.9 (PAD), U3.1 (GND); also elsewhere on the board
unnamed: C8.1, U3.2 (OUTPUT)
VCC: C2.1, C3.1, Q2.2 (D), U1.5 (EN/SYNC), U1.7 (VIN); also elsewhere on the board

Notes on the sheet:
LDO (5V -> 3v3)
16.8V Total?
LDO has a max current output of 1A

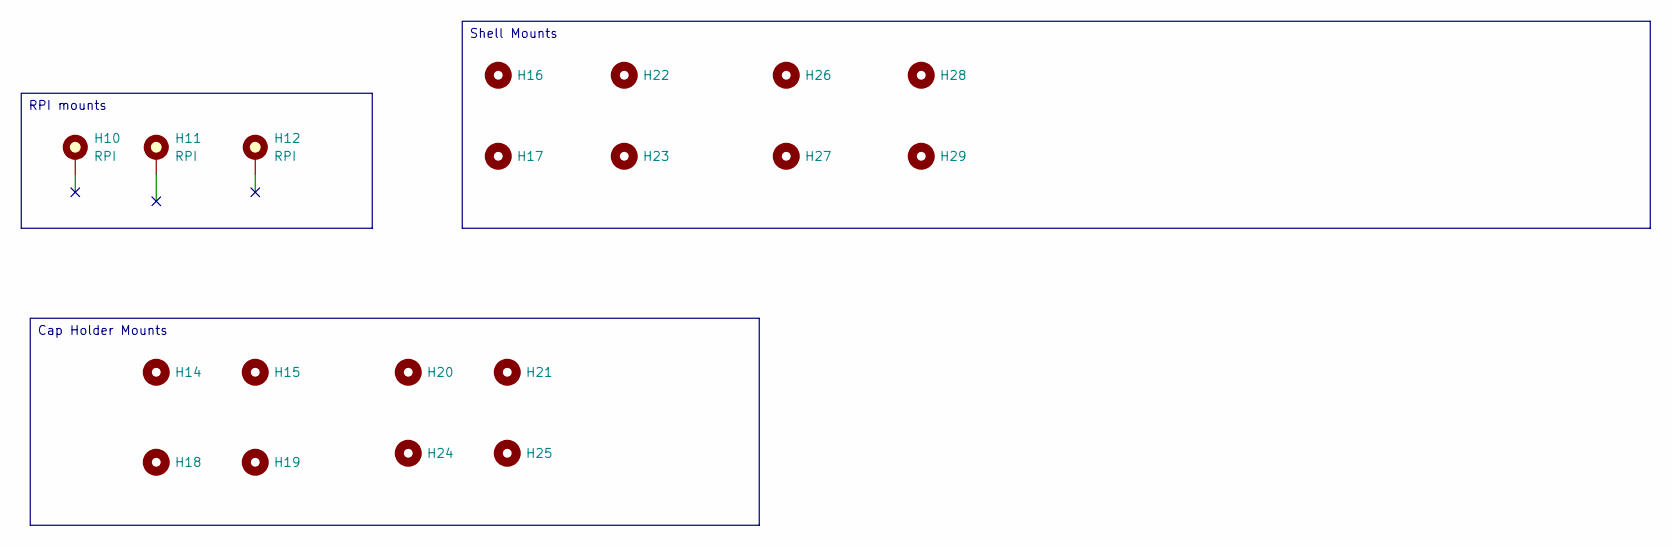
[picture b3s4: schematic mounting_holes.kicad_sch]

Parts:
H10, H11, H12: RPI; SMTSO2515CTJ
H14, H15, H16, H17, H18, H19, H20, H21, H22, H23, H24, H25, H26, H27, H28, H29: MountingHoleM2.5NoThread; MountingHole_2.7mm_M2.5_DIN965_Pad

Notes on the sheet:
Cap Holder Mounts
RPI mounts
Shell Mounts

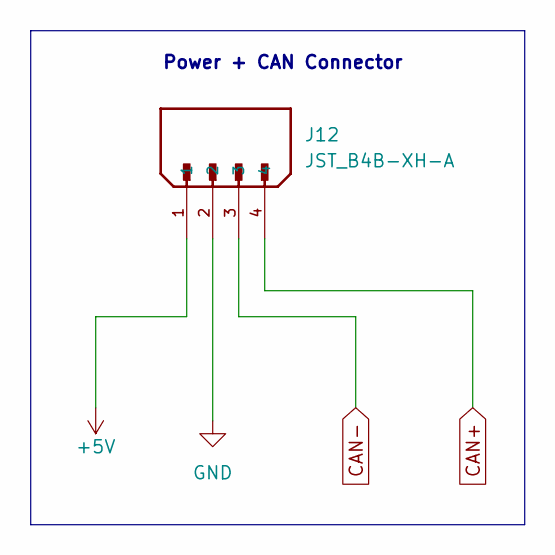
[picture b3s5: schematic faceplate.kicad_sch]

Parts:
J12: JST_B4B-XH-A; MPN B4B-XH-A(LF)(SN)

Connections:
+5V: J12.1; also elsewhere on the board
CAN+: J12.4; also elsewhere on the board
CAN-: J12.3; also elsewhere on the board
GND: J12.2; also elsewhere on the board

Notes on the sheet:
Power + CAN Connector

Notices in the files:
FacePlate/README.md:
License:
This project is licensed under the open-sourced MIT License - see the [LICENSE](LICENSE) file for details.
pmw3360-pcb-main/pmw3360_pcb_jst/pmw3360_pcb_jst.kicad_pcb:
Open Source Hardware, CERN-OHL-P v2
